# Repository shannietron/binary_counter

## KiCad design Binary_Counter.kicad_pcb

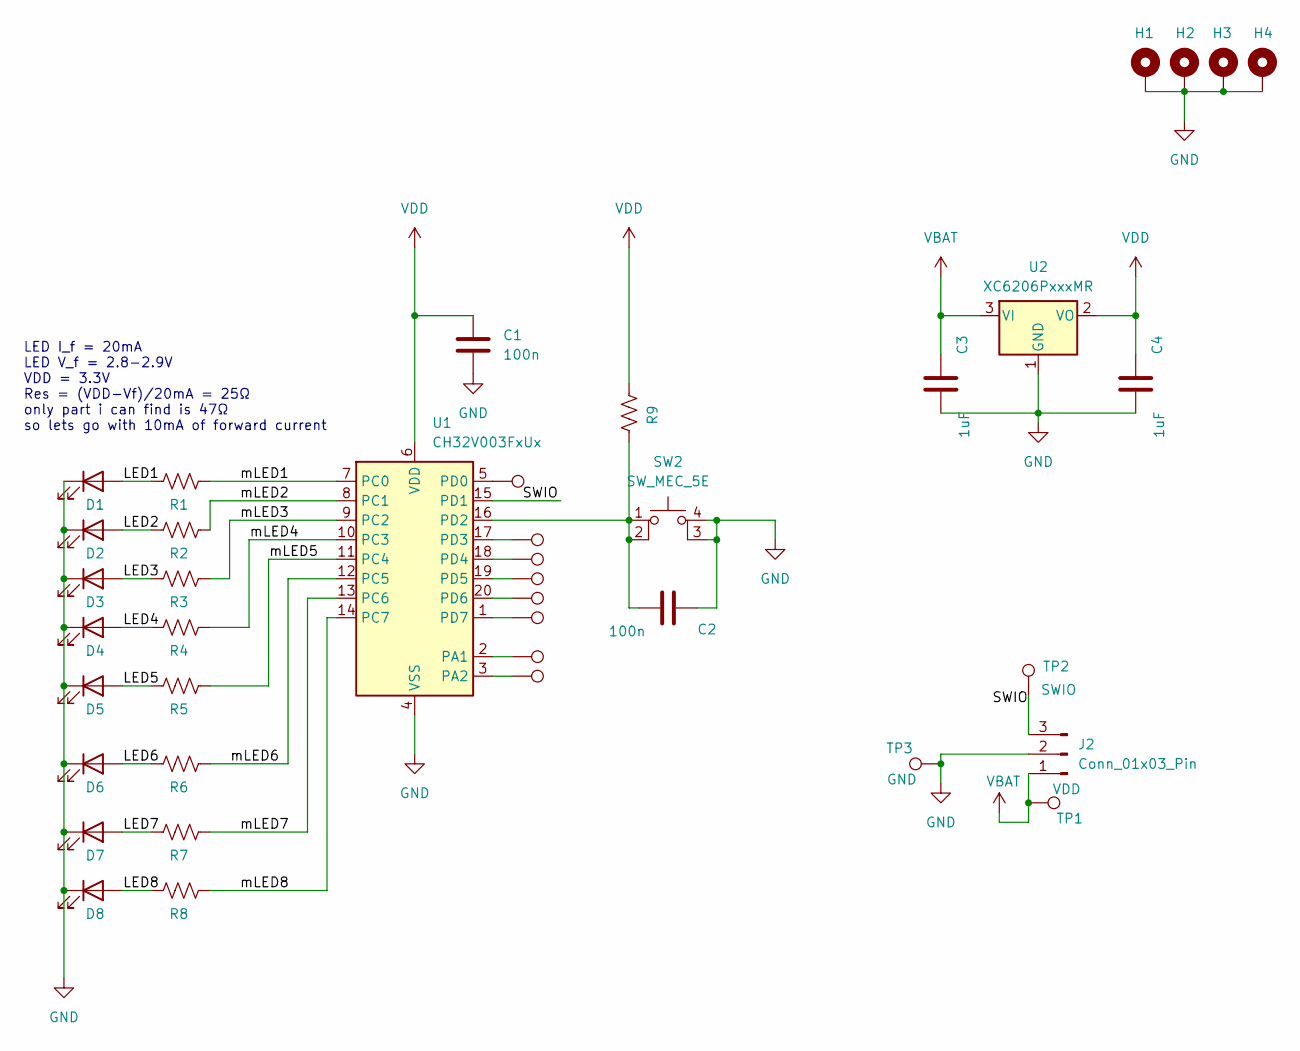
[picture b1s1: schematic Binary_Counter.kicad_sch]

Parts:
C1, C2: 100n; C_0805_2012Metric_Pad1.18x1.45mm_HandSolder
C3, C4: 1uF; C_0805_2012Metric_Pad1.18x1.45mm_HandSolder
D1, D2, D3, D4, D5, D6, D7, D8: LED; LED0805-R-RD
H1, H2, H3, H4: MountingHole_Pad; MountingHole_2.2mm_M2
J2: Conn_01x03_Pin; FanPinHeader_1x03_P2.54mm_Vertical
R1, R2, R3, R4, R5, R6, R7, R8, R9: R_US; R_0805_2012Metric_Pad1.20x1.40mm_HandSolder
SW2: SW_MEC_5E; SW-SMD_4P-L5.1-W5.1-P3.70-LS6.5-TL-2
TP1: VDD; TestPoint_Pad_D2.0mm
TP2: SWIO; TestPoint_Pad_D2.0mm
TP3: GND; TestPoint_Pad_2.0x2.0mm
TP4: PD3; TestPoint_Pad_D2.0mm
TP5: OPO; TestPoint_Pad_D2.0mm
TP6: PD5; TestPoint_Pad_D2.0mm
TP7: PD6; TestPoint_Pad_D2.0mm
TP8: PD7; TestPoint_Pad_D2.0mm
TP9: PA1; TestPoint_Pad_D2.0mm
TP10: PA2; TestPoint_Pad_D2.0mm
TP12: PD0; TestPoint_Pad_D2.0mm
U1: CH32V003FxUx; QFN-20-1EP_3x3mm_P0.4mm_EP1.65x1.65mm
U2: XC6206PxxxMR; SOT-23-3

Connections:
/LED1: D1.2 (A), R1.2
/LED2: D2.2 (A), R2.2
/LED3: D3.2 (A), R3.2
/LED4: D4.2 (A), R4.2
/LED5: D5.2 (A), R5.2
/LED6: D6.2 (A), R6.2
/LED7: D7.2 (A), R7.2
/LED8: D8.2 (A), R8.2
/SWIO: J2.3, TP2.1, U1.15 (PD1)
/mLED1: R1.1, U1.7 (PC0)
/mLED2: R2.1, U1.8 (PC1)
/mLED3: R3.1, U1.9 (PC2)
/mLED4: R4.1, U1.10 (PC3)
/mLED5: R5.1, U1.11 (PC4)
/mLED6: R6.1, U1.12 (PC5)
/mLED7: R7.1, U1.13 (PC6)
/mLED8: R8.1, U1.14 (PC7)
GND: C1.2, C2.2, C3.1, C4.1, D1.1 (K), D2.1 (K), D3.1 (K), D4.1 (K), D5.1 (K), D6.1 (K), D7.1 (K), D8.1 (K), H1.1, H2.1, H3.1, H4.1, J2.2, SW2.3 (K), SW2.4 (A), TP3.1, U1.4 (VSS), U1.21 (VSS), U2.1 (GND)
unnamed: TP9.1, U1.2 (PA1)
unnamed: TP10.1, U1.3 (PA2)
unnamed: TP12.1, U1.5 (PD0)
unnamed: C2.1, R9.2, SW2.1, SW2.2, U1.16 (PD2)
unnamed: TP4.1, U1.17 (PD3)
unnamed: TP5.1, U1.18 (PD4)
unnamed: TP6.1, U1.19 (PD5)
unnamed: TP7.1, U1.20 (PD6)
unnamed: TP8.1, U1.1 (PD7)
VBAT: C3.2, J2.1, TP1.1, U2.3 (VI)
VDD: C1.1, C4.2, R9.1, U1.6 (VDD), U2.2 (VO)

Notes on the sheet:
LED I_f = 20mA LED V_f = 2.8-2.9V VDD = 3.3V Res = (VDD-Vf)/20mA = 25Ω only part i can find is 47Ω so lets go with 10mA of forward current

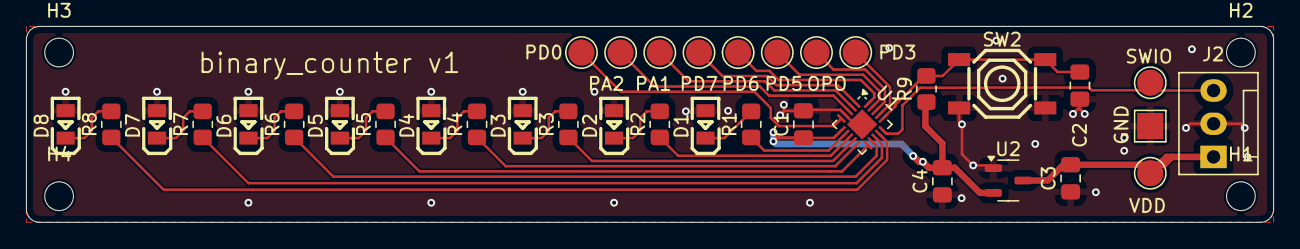
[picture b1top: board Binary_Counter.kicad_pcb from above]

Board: 2 copper layers, 95.5 x 15.0 mm, 40 parts (0 on the bottom side), 29 nets.

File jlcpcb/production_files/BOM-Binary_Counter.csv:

Comment,Designator,Footprint,LCSC
LED,"D1,D2,D3,D4,D5,D6,D7,D8",LED0805-R-RD,C2297
R_US,"R1,R2,R3,R4,R5,R6,R7,R8,R9",R_0805_2012Metric_Pad1.20x1.40mm_HandSolder,C23182
1uF,"C3,C4",C_0805_2012Metric_Pad1.18x1.45mm_HandSolder,C28323
SW_MEC_5E,SW2,SW-SMD_4P-L5.1-W5.1-P3.70-LS6.5-TL-2,C318884
100n,"C1,C2",C_0805_2012Metric_Pad1.18x1.45mm_HandSolder,C49678
CH32V003FxUx,U1,QFN-20-1EP_3x3mm_P0.4mm_EP1.65x1.65mm,C5299908
XC6206PxxxMR,U2,SOT-23-3,C5446

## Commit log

2024-05-30 add .gitignore
2024-05-30 init kicad files
2024-05-31 move switch to PD2, add debouncing to switch
2024-06-02 add 8 LEDs total and add a 3 pin connector for power and SWIO
2024-06-06 initial placement of components on board
2024-06-30 complete routing
2024-06-30 add revision to silk
2024-06-30 add M2 mounting holes
2024-06-30 generate interactive bom
2024-06-30 move index.html to /bom/index.html
2024-06-30 rename ibom.html to index.html
2024-06-30 move index.html to /docs so that github can publish it as pages
2024-06-30 add url to back silk
2024-07-01 add 3V3 LDO
2024-07-01 place and route LDO
2024-07-01 generate ibom
2024-07-02 add design rules from jlc template, fix errors
2024-07-02 add JLC production files
2024-07-23 add enclosure outline to layers user.6 and user.7 to generate enclosure with turbocase
2024-07-31 make mounting screws M2 and M3 self tapping.
2024-07-31 add LED holes
2024-08-14 update enclosure to have thin plastic walls for light and optimise M2 and M3 screws for self tapping
